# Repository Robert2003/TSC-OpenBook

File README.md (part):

# README - OpenBook

## Diagrama bloc
```mermaid
graph LR;
    USB["USB-C Connector & ESD Protection"] -->|VBUS| CHG
    BATT["Li-Po Battery"] -->|VBAT| CHG["Battery Charging Controller (MCP73831)"]
    USB -->|VBUS pass-through| LDO["LDO Voltage Regulator (XC6220)"]
    USB -->|USB| ESP["ESP32-C6 MICROCONTROLLER Wi-Fi (MCU Central)"]
    CHG -->|VBAT| LDO
    LDO -->|3.3V| ESP["ESP32-C6 MICROCONTROLLER Wi-Fi (MCU Central)"]

    ESP -->|I2C| RTC["RTC Module (DS3231SN)"]
    ESP -->|I2C| BME["Environmental Sensor (BME680)"]

    ESP -->|SPI| FLASH["External NOR Flash (W25Q512)"]
    ESP -->|SPI| EPD_HEADER["E-Paper Display Header"]
    ESP -->|SPI| SD["MicroSD Card"]
    ESP -->|GPIO| BUTTONS["BOOT, CHANGE, RESET Buttons"]
    ESP -->|GPIO| VSUP["Voltage Supervisor + Reset/Boot IO"]

    EPD_HEADER -->|Power, SPI| EPD_DRIVER["E-Paper Drive Circuit"]
    EPD_DRIVER -->|Type Config| DISP_SEL["Display Type Selector"]
    EPD_DRIVER -->|High Voltage| EPD_POW["EPD Power Circuit"]

    I2C_CONN["Qwiic / Stemma QT"] -->|I2C| ESP
    BAT_LVL["Battery Charge Level"] -->|I2C| ESP
    SERCOM["RX/TX Serial Communication"] --> ESP
```
---

## Funcționalitatea hardware

### Microcontroller principal
- ESP32-C6-WROOM-1-N8
  - Procesor RISC-V 32-bit
  - Conectivitate Wi-Fi 6 și Bluetooth 5.0
  - 8MB Flash (intern)
  - Alimentare 3.3V
  - Niveluri logice 3.3V

### Componente periferice și interfețe

| Componentă                      | Ref. Schematică | Interfață    | Pini ESP32 Utilizați / Descriere                                        |
| :------------------------------ | :-------------- | :----------- | :---------------------------------------------------------------------- |
| Ecran EPD (e-paper)             | J4              | SPI + GPIO   | SPI (IO7, IO27, IO6), CS (IO11), DC (IO5), RST (IO21), BUSY (IO26)      |
| Slot Card MicroSD               | J3              | SPI          | SPI (IO7=MOSI/DI, IO27=MISO/DO, IO6=SCK), CS (IO10)                       |
| Interfață USB                   | J2              | USB Native   | D- (IO13), D+ (IO14) via protecție ESD (D2)                             |
| RTC (Real Time Clock)           | IC2             | I2C          | SDA (IO19), SCL (IO20); Include Supercap (C10) pentru backup           |
| Senzor Temp/Umid/Pres/Gaz (BME) | IC3             | I2C          | SDA (IO19), SCL (IO20)                                                  |
| Încărcător Li-Po                | IC1             | Power        | MCP73831; Indicator LED încărcare (D4)                                  |
| Regulator LDO 3.3V              | IC4             | Power        | XC6220A331MR-G                                                          |
| Circuit Reset / Supraveghere    | IC5             | Power/Control| BD5229G-TR                                                              |
| Buton BOOT                      | SW1             | GPIO         | Conectat la IO8                                                         |
| Buton RESET                     | SW2             | Reset        | Conectat la linia RESET                                                 |
| MOSFET comutare EPD Power       | Q1, Q2          | Control      | Comută alimentarea 3V3_EPD                                              |

#### SPI (Serial Peripheral Interface)
- **Utilizat pentru EPD și Card SD.**
- **MOSI** (Master Out Slave In): **IO7**
- **MISO** (Master In Slave Out): **IO27**
- **SCK** (Serial Clock): **IO6**
- **SS / CS** (Slave Select / Chip Select):
    - **EPD_CS**: **IO11**
    - **SD_CS**: **IO10**

#### I2C (Inter-Integrated Circuit)
- **Utilizat pentru RTC (IC2) și Senzor BME (IC3).**
- **SDA** (Serial Data): **IO19**
- **SCL** (Serial Clock): **IO20**

#### GPIO (General Purpose Input/Output) & Alți Pini
- **EPD_DC** (Data/Command): **IO5**
- **EPD_RST** (Reset): **IO21**
- **EPD_BUSY**: **IO26**
- **USB_D-**: **IO13**
- **USB_D+**: **IO14**
- **BOOT_PIN**: **IO8**
- **RESET_PIN**: **IO3**
- **EN** (Enable): Conectat la 3.3V

## Detaliere Pini Utilizați (ESP32-C6 / U2)

| Pin ESP32 | Funcție Principală                  | Componentă Conectată / Scop                  |
| :-------- | :---------------------------------- | :------------------------------------------- |
| IO0       | GPIO                                | INT_RTC (ieșire din RTC)                     |
| IO1       | GPIO                                | 32KHZ (ieșire ceas RTC)                      |
| IO2       | SPI MISO                            | MISO (EPD + SD)                              |
| IO3       | GPIO                                | SS_SD (chip select pentru SD)                |
| IO4       | GPIO                                | EPD_BUSY                                     |
| IO5       | GPIO                                | EPD_DC                                       |
| IO6       | SPI SCK                             | SCK (EPD + SD)                               |
| IO7       | SPI MOSI                            | MOSI (EPD + SD)                              |
| IO8       | GPIO                                | IO/BOOT (buton boot)                         |
| IO10      | GPIO                                | EPD_CS                                       |
| IO11      | GPIO                                | FLASH_CS                                     |
| IO12      | GPIO                                | Neutilizat                                   |
| IO13      | USB D-                              | USB_D- (conector USB-C)                      |
| IO14      | USB D+                              | USB_D+ (conector USB-C)                      |
| IO16      | UART TX                             | TX                                           |
| IO17      | UART RX                             | RX                                           |
| IO18      | GPIO                                | RTC_RST                                      |
| IO19      | GPIO                                | I2C_PW (putere I2C)                          |
| IO20      | I2C SDA                             | SDA (RTC + BME280)                           |
| IO21      | I2C SCL                             | SCL (RTC + BME280)                           |
| IO22      | GPIO                                | EPD_RST                                      |
| IO23      | GPIO                                | Neconectat                                   |
| IO25      | GPIO                                | IO/CHANGE                                    |
| IO26      | GPIO                                | EPD_BUSY                                     |
| IO27      | SPI MISO                            | 32KHZ (ceas RTC)                             |
| EN        | Enable                              | Buton RESET (pull-up la 3.3V)                |
| VDD (3V3) | Alimentare                          | 3.3V                                         |
| GND       | Masă                                | GND                                          |

---

##  Bill of Materials

| Device                                                     | Datasheet                                                                                                                                                                                                                                                                                                                                                                                                                                                                                                                                                                                                                                                                                                                                                                                                                                                                                                                                                                                                                                                                                                                             | Purchase URL                                                                                               |
| :--------------------------------------------------------- | :------------------------------------------------------------------------------------------------------------------------------------------------------------------------------------------------------------------------------------------------------------------------------------------------------------------------------------------------------------------------------------------------------------------------------------------------------------------------------------------------------------------------------------------------------------------------------------------------------------------------------------------------------------------------------------------------------------------------------------------------------------------------------------------------------------------------------------------------------------------------------------------------------------------------------------------------------------------------------------------------------------------------------------------------------------------------------------------------------------------------------ | :--------------------------------------------------------------------------------------------------------- |
| ADAFRUIT_LEDCHIP-LED0603                                   | [Datasheet](https://www.mouser.com/datasheet/2/423/LSM0603472V_(1)-1379786.pdf) | [Purchase](https://componentsearchengine.com/part-view/LSM0603463V/Visual%20Communications%20Company)                 |
| BUTTON_CUSYOMV1                                            | [Datasheet](https://industry.panasonic.com/global/en/downloads?tab=catalog&small_g_cd=203&part_no=EVQPUJ02K)                                                                                                                                                                                                                                                                                                                                                                                                                                                                                                                                                                                                                                                                                                                                                                                                                                                                                                                                                                                                                                 | [Purchase](https://industry.panasonic.com/global/en/products/control/switch/light-touch/number/evqpuj02k)              |
| ESP32C6_VARISTORCN1812                                     | [Datasheet](https://www.tdk-electronics.tdk.com/inf/75/db/CTVS_14/Surge_protection_series.pdf)                                                                                                                                                                                                                                                                                                                                                                                                                                                                                                                                                                                                                                                                                                                                                                                                                                                                                                                                                                                                                                              | [Purchase](https://www.mouser.co.uk/ProductDetail/EPCOS-TDK/B72520T0350K062?qs=dEfas%2FXlABIszF52uu7vrg%3D%3D)          |
| ESP32_WROVER_SPARKFUN-IC-POWER_MCP73831                    | [Datasheet](https://ro.mouser.com/datasheet/2/268/MCP73831_Family_Data_Sheet_DS20001984H-3441711.pdf)                                                                                                                                                                                                                                                                                                                                                                                                                                                                                                                                                                                                                                                                                                                                                                                                                                                                                                                                                                                                                                         | [Purchase](https://ro.mouser.com/ProductDetail/Microchip-Technology/MCP73831T-5ACI-OT?qs=hH%252BOa0VZEiAcgAcEkuamXg%3D%3D) |
| SAMACSYS_PARTS_USB4110-GF-A                                | [Datasheet](https://ro.mouser.com/datasheet/2/837/GCT_USB4110_Product_Drawing___20k_cycles-3455479.pdf)                                                                                                                                                                                                                                                                                                                                                                                                                                                                                                                                                                                                                                                                                                                                                                                                                                                                                                                                                                                                                                         | [Purchase](https://componentsearchengine.com/part-view/XC6220A331MR-G/Torex)                                         |
| SJ                                                         | [Datasheet](https://analytics.supplyframe.com/trackingservlet/track/?r=0x34EY99PS_gIu2qWuzU9_U842M9-un2szqNoXX0OQ9lqbiEKGN3BJ73jgvlrgiXR89Peb0evqc4GXoUXllBhuC-t-jUChl_ve9sxyIbn9itd6HouwDNkBJ6EbvJG_W1dvQ33O37oQvrBIGmAmWf7WaTE1x7V-fhYVb8BzYSgNk10lRrx9ydF05rSu_yF-RcTLzrvVqKpyEMsu1tWML3F5NsDK3eYvMDWLFReFpcpYcQT6VJIIHxe2IkeuwFaNGGth_bPArqAVRLfjMYZDlSoV5_e61wrdrMeBLi53h3S0fpxDEX4TLvuLsi8JJGhgQx2voMmyqY6gjXW05FuTS5Qg0wN73a4RXBC7fJniBn8yriZXPMyggVMPVjL_9j3a1i4URi-pLFft7-_hLLLd0kX-uUouNvW0LzSWKkqNJlO6y1UWqDYMRLOE2dWFnrHj_3dksoFiwKXmoFw3sFOj5NXRaA6wxikMMMYZ3-gooWmAhCzEczgqDfXEQesLsiJT4-XFNfgt7LRuH9NmM38ieQHEqyxGFi6kd4X6I0KTHQLg2-V8XlyekPtBCU8gDdPBhOQ17Oj7rYC0lA0EcA__td0qxqTJ8t7VxJcv7gPOP6anfgCpsnupcmJj6zFPjIrtqj4NWwwbbecRBKOv7doyTdwmzqoyGGrGPY7DQKSHciWg8cX6Hc3D7dmNS4mPEOJOOKewle43KybI4UJMP_UcC5JA) | [Purchase](https://componentsearchengine.com/part-view/R0402%201%25%20100%20K%20(RC0402FR-07100KL)/YAGEO)              |
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
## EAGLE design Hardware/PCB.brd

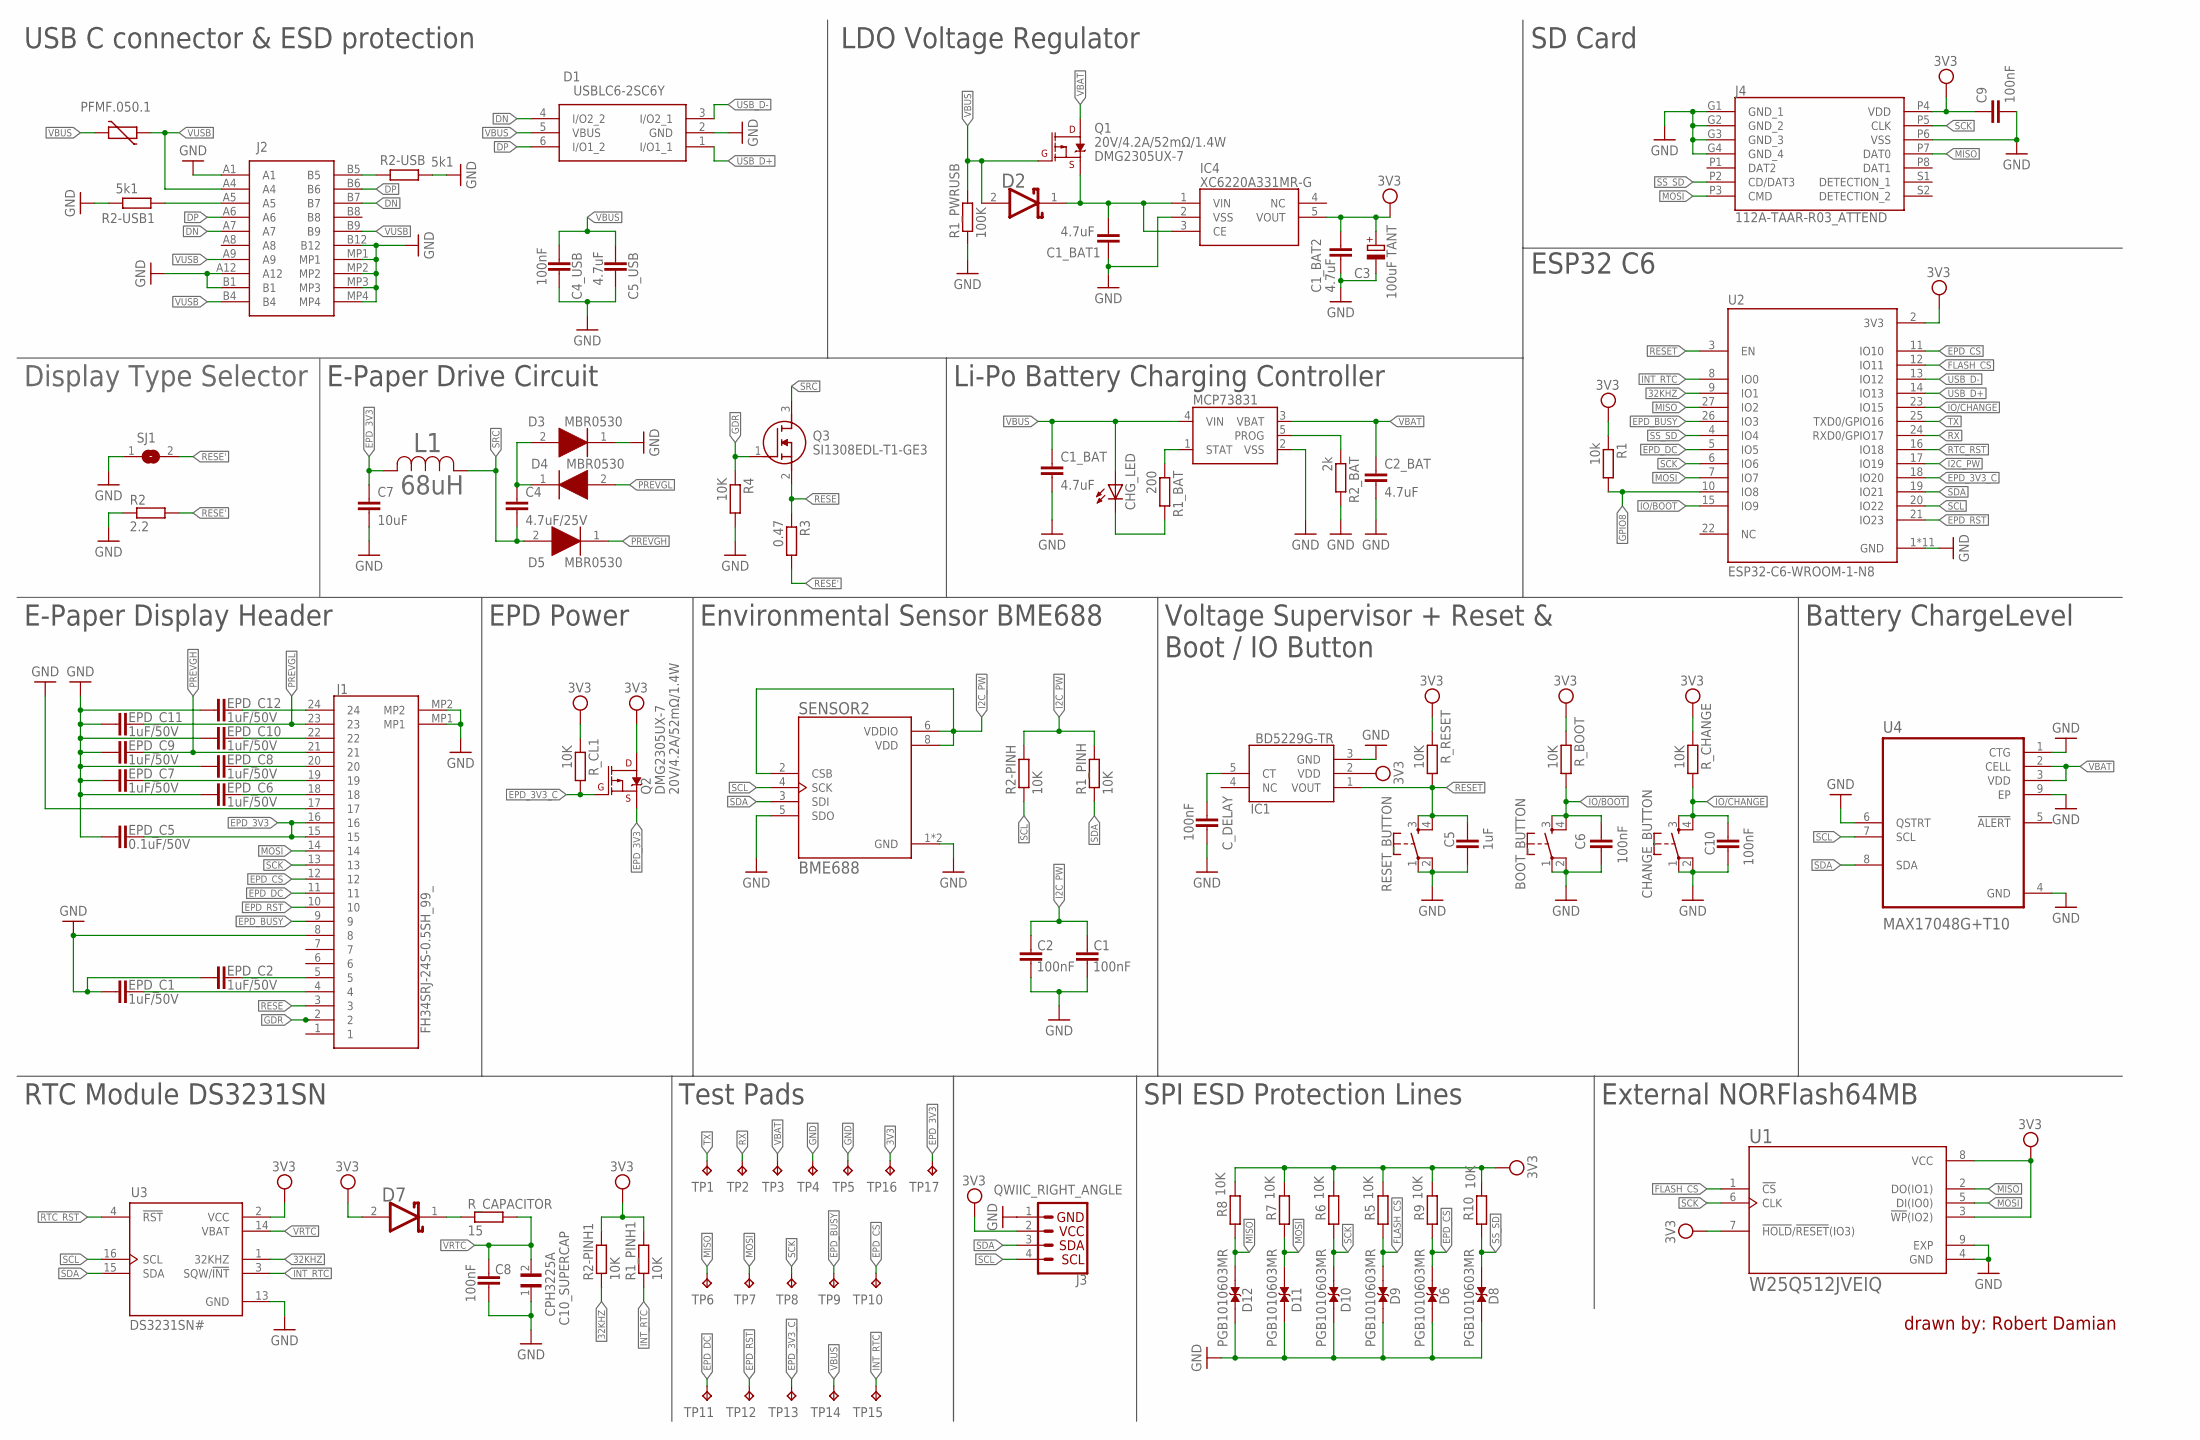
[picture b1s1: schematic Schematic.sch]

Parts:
BOOT_BUTTON: BUTTON_CUSYOMV1; MYBUTTON
C1, C2, C4_USB, C6, C8, C9, C10: 100nF; EAGLE-LTSPICE_C0402
C1_BAT, C1_BAT1, C1_BAT2, C2_BAT, C5_USB: 4.7uF; EAGLE-LTSPICE_C0402
C3: 100uF TANT; RCL_CT3528
C4: 4.7uF/25V; EAGLE-LTSPICE_C0402
C5: 1uF; EAGLE-LTSPICE_C0402
C7: 10uF; EAGLE-LTSPICE_C0402
C10_SUPERCAP: CPH3225A; CAPCP3225X100N
CHANGE_BUTTON: BUTTON_CUSYOMV1; MYBUTTON
CHG_LED: ADAFRUIT_LEDCHIP-LED0603; ADAFRUIT_CHIP-LED0603
C_DELAY: 100nF; EAGLE-LTSPICE_C0402
D1: USBLC6-2SC6Y; SOT95P280X145-6N
D2, D7: SD0805S020S1R0; ESP32_WROVER_AVX---SD0805S020S1R0_AVX_SD0805S020S1R0_0
D3, D4, D5: MBR0530; SOD3716X135N
D6, D8, D9, D10, D11, D12: PGB1010603MR; DIOC1608X36N
EPD_C1, EPD_C2, EPD_C6, EPD_C7, EPD_C8, EPD_C9, EPD_C10, EPD_C11, EPD_C12: 1uF/50V; EAGLE-LTSPICE_C0402
EPD_C5: 0.1uF/50V; EAGLE-LTSPICE_C0402
IC1: BD5229G-TR; SOT95P280X125-5N
IC4: XC6220A331MR-G; SOT95P280X120-5N
J1: FH34SRJ-24S-0.5SH_99_; FH34SRJ24S05SH99
J2: SAMACSYS_PARTS_USB4110-GF-A; SAMACSYS_PARTS_USB4110GFA
J3: QWIIC_RIGHT_ANGLE; JST04_1MM_RA
J4: 112A-TAAR-R03_ATTEND; 112ATAARR03ATTEND
L1: 68uH; IND_4828-WE-TPC_WRE
MCP73831: ESP32_WROVER_SPARKFUN-IC-POWER_MCP73831; ESP32_WROVER_SPARKFUN-IC-POWER_SOT23-5
PFMF.050.1: ESP32C6_VARISTORCN1812; ESP32C6_VARISTOR_CT/CN1812
Q1, Q2: 20V/4.2A/52mΩ/1.4W; ESP32_WROVER_SPARKFUN-DISCRETESEMI_SOT23-3
Q3: SI1308EDL-T1-GE3; SOT65P210X110-3N
R1: 10k; ESP32_WROVER_EAGLE-LTSPICE_R0402
R1_BAT: 200; ESP32_WROVER_EAGLE-LTSPICE_R0402
R1_PINH, R1_PINH1, R2-PINH, R2-PINH1, R4, R5, R6, R7, R8, R9, R10: 10K; ESP32_WROVER_EAGLE-LTSPICE_R0402
R1_PWRUSB: 100K; ESP32_WROVER_EAGLE-LTSPICE_R0402
R2: 2.2; ESP32_WROVER_EAGLE-LTSPICE_R0402
R2-USB, R2-USB1: 5k1; ESP32_WROVER_EAGLE-LTSPICE_R0402
R2_BAT: 2k; ESP32_WROVER_EAGLE-LTSPICE_R0402
R3: 0.47; ESP32_WROVER_EAGLE-LTSPICE_R0402
RESET_BUTTON: BUTTON_CUSYOMV1; MYBUTTON
R_BOOT: 10K; ESP32_WROVER_EAGLE-LTSPICE_R0402
R_CAPACITOR: 15; ESP32_WROVER_EAGLE-LTSPICE_R0402
R_CHANGE: 10K; ESP32_WROVER_EAGLE-LTSPICE_R0402
R_CL1: 10K; ESP32_WROVER_EAGLE-LTSPICE_R0402
R_RESET: 10K; ESP32_WROVER_EAGLE-LTSPICE_R0402
SENSOR2: BME688; ESP32_WROVER_BME680_PSON80P300X300X100-8N
SJ1: SJ; ESP32_WROVER_EAGLE-LTSPICE_R0402
TP1, TP2, TP3, TP4, TP5, TP6, TP7, TP8, TP9, TP10, TP11, TP12, TP13, TP14, TP15, TP16, TP17: TPTP20R; TP20R
U1: W25Q512JVEIQ; SON127P600X800X80-9N
U2: ESP32-C6-WROOM-1-N8; XCVR_ESP32-C6-WROOM-1-N8
U3: DS3231SN#; SOIC127P1032X265-16N
U4: MAX17048G+T10; SON50P200X200X80-9N

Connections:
3V3: C1_BAT2.1, C3.+, C9.1, D7.2 (ANODE), IC1.2 (VDD), IC4.5 (VOUT), J3.2, J4.P4 (VDD), Q2.3 (D), R1.1, R1_PINH1.2, R2-PINH1.2, R5.2, R6.2, R7.2, R8.2, R9.2, R10.2, R_BOOT.1, R_CHANGE.1, R_CL1.1, R_RESET.1, TP16.TP, U1.3 (!WP!(IO2)), U1.7 (!HOLD!/!RESET!(IO3)), U1.8 (VCC), U2.2 (3V3), U3.2 (VCC)
32KHZ: R2-PINH1.1, U2.9 (IO1), U3.1 (32KHZ)
DN: D1.4 (I/O2_2), J2.A7, J2.B7
DP: D1.6 (I/O1_2), J2.A6, J2.B6
EPD_3V3: C7.1, EPD_C5.1, J1.15, J1.16, L1.2, Q2.2 (S), TP17.TP
EPD_3V3_C: Q2.1 (G), R_CL1.2, TP13.TP, U2.18 (IO20)
EPD_BUSY: J1.9, TP9.TP, U2.26 (IO3)
EPD_CS: D6.1, J1.12, R9.1, TP10.TP, U2.11 (IO10)
EPD_DC: J1.11, TP11.TP, U2.5 (IO5)
EPD_RST: J1.10, TP12.TP, U2.21 (IO23)
FLASH_CS: D9.1, R5.1, U1.1 (!CS), U2.12 (IO11)
GDR: J1.2, Q3.1 (G), R4.1
GND: BOOT_BUTTON.1, BOOT_BUTTON.2, C1.2, C1_BAT.2, C1_BAT1.2, C1_BAT2.2, C2.2, C2_BAT.2, C3.-, C4_USB.2, C5.2, C5_USB.2, C6.2, C7.2, C8.2, C9.2, C10.2, C10_SUPERCAP.1, CHANGE_BUTTON.1, CHANGE_BUTTON.2, C_DELAY.2, D1.2 (GND), D3.1 (K), D6.2, D8.2, D9.2, D10.2, D11.2, D12.2, EPD_C1.2, EPD_C2.2, EPD_C5.2, EPD_C6.2, EPD_C7.2, EPD_C8.2, EPD_C9.2, EPD_C10.2, EPD_C11.2, EPD_C12.2, IC1.3 (GND), IC4.2 (VSS), J1.8, J1.17, J1.MP1, J1.MP2, J2.A1, J2.A12, J2.B1, J2.B12, J2.MP1, J2.MP2, J2.MP3, J2.MP4, J3.1, J4.G1 (GND_1), J4.G2 (GND_2), J4.G3 (GND_3), J4.G4 (GND_4), J4.P6 (VSS), MCP73831.2 (VSS), R1_PWRUSB.1, R2.1, R2-USB.1, R2-USB1.1, R2_BAT.2, R4.2, RESET_BUTTON.1, RESET_BUTTON.2, SENSOR2.1 (GND), SENSOR2.5 (SDO), SENSOR2.7 (GND), SJ1.1, TP4.TP, TP5.TP, U1.4 (GND), U1.9 (EXP), U2.1 (GND), U2.28 (GND), U2.29_1 (GND), U2.29_2 (GND)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
GPIO8: R1.2, U2.10 (IO8)
I2C_PW: C1.1, C2.1, R1_PINH.2, R2-PINH.2, SENSOR2.2 (CSB), SENSOR2.6 (VDDIO), SENSOR2.8 (VDD), U2.17 (IO19)
INT_RTC: R1_PINH1.1, TP15.TP, U2.8 (IO0), U3.3 (SQW/!INT)
IO/BOOT: BOOT_BUTTON.3, BOOT_BUTTON.4, C6.1, R_BOOT.2, U2.15 (IO9)
IO/CHANGE: C10.1, CHANGE_BUTTON.3, CHANGE_BUTTON.4, R_CHANGE.2, U2.23 (IO15)
MISO: D12.1, J4.P7 (DAT0), R8.1, TP6.TP, U1.2 (DO(IO1)), U2.27 (IO2)
MOSI: D11.1, J1.14, J4.P3 (CMD), R7.1, TP7.TP, U1.5 (DI(IO0)), U2.7 (IO7)
unnamed: J2.A5, R2-USB1.2
unnamed: J2.B5, R2-USB.2
unnamed: EPD_C12.1, J1.24
unnamed: C1_BAT1.1, D2.1 (CATHODE), IC4.1 (VIN), IC4.3 (CE), Q1.2 (S)
unnamed: CHG_LED.C, R1_BAT.2
unnamed: C4.1, D3.2 (A), D4.1 (K)
unnamed: MCP73831.1 (STAT), R1_BAT.1
unnamed: MCP73831.5 (PROG), R2_BAT.1
unnamed: EPD_C2.1, J1.5
unnamed: EPD_C10.1, J1.22
unnamed: EPD_C1.1, J1.4
unnamed: EPD_C8.1, J1.20
unnamed: EPD_C7.1, J1.19
unnamed: EPD_C6.1, J1.18
unnamed: C_DELAY.1, IC1.5 (CT)
unnamed: D7.1 (CATHODE), R_CAPACITOR.1
PREVGH: D5.1 (K), EPD_C9.1, J1.21
PREVGL: D4.2 (A), EPD_C11.1, J1.23
RESE: J1.3, Q3.2 (S), R3.1
RESE': R2.2, R3.2, SJ1.2
RESET: C5.1, IC1.1 (VOUT), RESET_BUTTON.3, RESET_BUTTON.4, R_RESET.2, U2.3 (EN)
RTC_RST: U2.16 (IO18), U3.4 (!RST)
RX: TP2.TP, U2.24 (RXD0/GPIO17)
SCK: D10.1, J1.13, J4.P5 (CLK), R6.1, TP8.TP, U1.6 (CLK), U2.6 (IO6)
SCL: J3.4, R2-PINH.1, SENSOR2.4 (SCK), U2.20 (IO22), U3.16 (SCL), U4.7 (SCL)
SDA: J3.3, R1_PINH.1, SENSOR2.3 (SDI), U2.19 (IO21), U3.15 (SDA), U4.8 (SDA)
SRC: C4.2, D5.2 (A), L1.1, Q3.3 (D)
SS_SD: D8.1, J4.P2 (CD/DAT3), R10.1, U2.4 (IO4)
TX: TP1.TP, U2.25 (TXD0/GPIO16)
USB_D+: D1.1 (I/O1_1), U2.14 (IO13)
USB_D-: D1.3 (I/O2_1), U2.13 (IO12)
VBAT: C2_BAT.1, MCP73831.3 (VBAT), Q1.3 (D), TP3.TP, U4.2 (CELL), U4.3 (VDD)
VBUS: C1_BAT.1, C4_USB.1, C5_USB.1, CHG_LED.A, D1.5 (VBUS), D2.2 (ANODE), MCP73831.4 (VIN), PFMF.050.1.2, Q1.1 (G), R1_PWRUSB.2, TP14.TP
VRTC: C8.1, C10_SUPERCAP.2, R_CAPACITOR.2, U3.14 (VBAT)
VUSB: J2.A4, J2.A9, J2.B4, J2.B9, PFMF.050.1.1

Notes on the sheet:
USB C connector & ESD protection
LDO Voltage Regulator
SD Card
ESP32 C6
Display Type Selector
E-Paper Drive Circuit
Li-Po Battery Charging Controller
E-Paper Display Header
EPD Power
Environmental Sensor BME688
Voltage Supervisor + Reset & Boot / IO Button
Battery ChargeLevel
RTC Module DS3231SN
Test Pads
SPI ESD Protection Lines
External NORFlash64MB
DMG2305UX-7
drawn by: Robert Damian

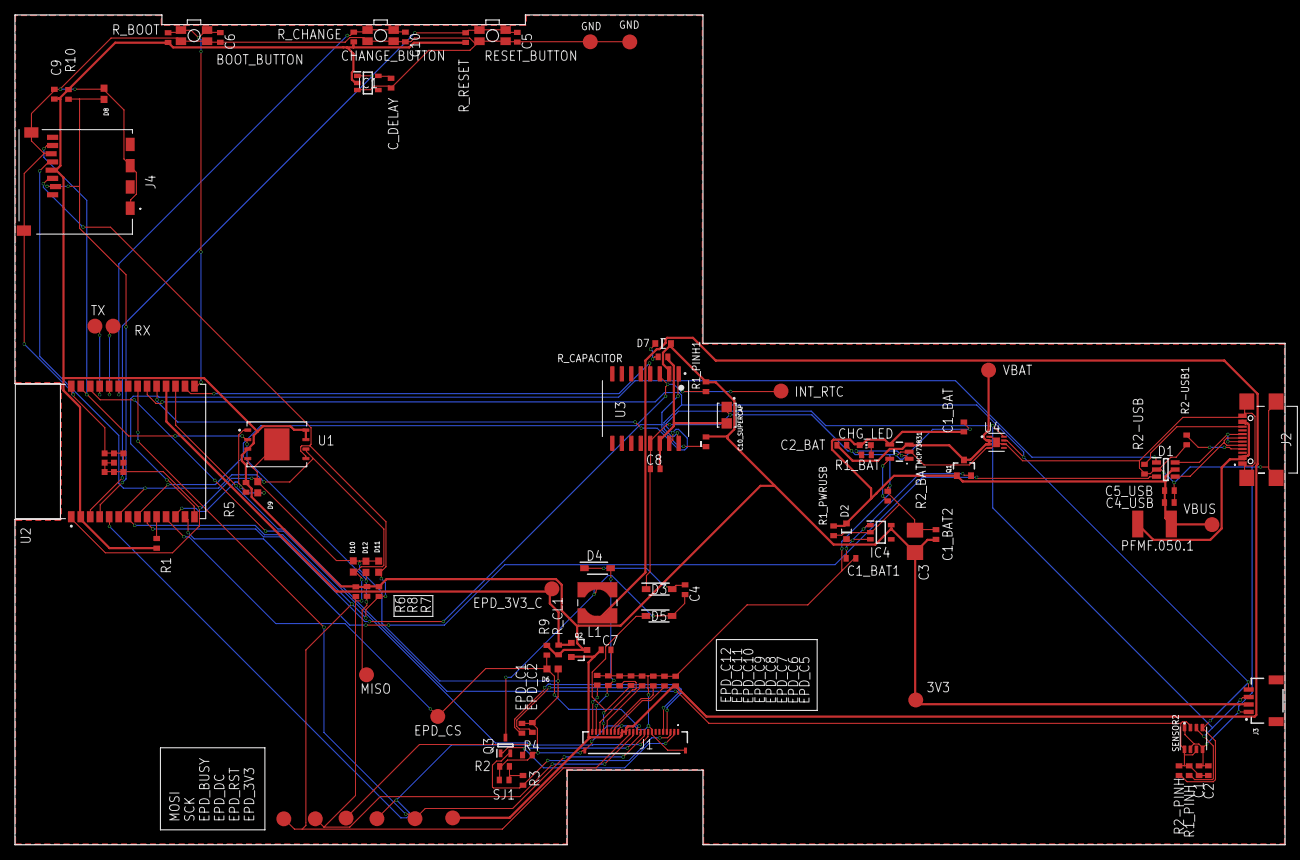
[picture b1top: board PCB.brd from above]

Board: 2 copper layers, 170.2 x 111.2 mm, 103 parts (0 on the bottom side), 55 nets.

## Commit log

2025-04-05 Finished model, missing README
2025-04-05 Create LICENSE
2025-04-06 readme
2025-04-06 Updated 3d Model
2025-04-06 Diagrama
2025-04-06 Updated Hardware
2025-04-13 Solved all issues

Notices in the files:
parts and their libraries:
COPYRIGHT: Copyright (C) 2024 Ultra Librarian. All rights reserved.
